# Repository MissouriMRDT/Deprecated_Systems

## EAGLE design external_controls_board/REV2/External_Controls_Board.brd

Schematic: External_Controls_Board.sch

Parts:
+5V, +12V: APPPP45_PCB_VERT; APP45_PCB_VERT
CAP_TOOL: .1µF; 0603-CAP
FET_PWRMAIN: BUK9Y4R4-40EPOWER-SO8; POWER-SO8
FET_TOOL: BUK9Y4R4-40EPOWER-SO8; POWER-SO8
GND: APPPP45_PCB_VERT; APP45_PCB_VERT
LT1910-J2, LT1910-MAIN: LT1910; SO8
LT1910CAP-MAIN: .1µF; 0603-CAP
S00, S01, S02, S03, S10, S11, S12, S13, S20, S21, S22, S23, S30, S31, S32, S33: SERVO; SERVO_JACK
U$1, U$8: SN74AHCT125; SOIC14
U$2: TIVA-C-CONNECTED
U$3, U$11: APPPP45_PCB_VERT; APP45_PCB_VERT
U$4, U$9: M07; MOLEX_43650-07
U$6: MOUNTING_HOLE#8; #8_SCREW
U$10: ACS722; SO-08

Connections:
+3V3: U$10.8 (VCC)
+5V: +5V.P$1, S00.VCC (+5V), S01.VCC (+5V), S02.VCC (+5V), S03.VCC (+5V), S10.VCC (+5V), S11.VCC (+5V), S12.VCC (+5V), S13.VCC (+5V), S20.VCC (+5V), S21.VCC (+5V), S22.VCC (+5V), S23.VCC (+5V), S30.VCC (+5V), S31.VCC (+5V), S32.VCC (+5V), S33.VCC (+5V), U$1.14 (VCC), U$2.+5V_1 (+5V), U$2.+5V_2 (+5V), U$8.14 (VCC)
+12V: CAP_TOOL.2, FET_TOOL.5 (D), FET_TOOL.6 (D), FET_TOOL.7 (D), FET_TOOL.8 (D), LT1910-J2.6 (SENSE), LT1910-J2.8 (V+), U$4.P_6 (6), U$9.P_6 (6), U$10.3 (IP-), U$10.4 (IP-)
BPWM0_3.3: U$2.PA5, U$8.12 (4A)
BPWM1_3.3: U$2.PA4, U$8.9 (3A)
BPWM2_3.3: U$2.PD5, U$8.5 (2A)
BPWM3_3.3: U$2.PD4, U$8.2 (1A)
DYNA_DATA: U$2.PC4, U$2.PC5, U$4.P_5 (5), U$9.P_5 (5)
GATE-J2: FET_TOOL.4 (G), LT1910-J2.5 (GATE)
GATE-MAIN: FET_PWRMAIN.4 (G), LT1910-MAIN.5 (GATE)
GND: CAP_TOOL.1, GND.P$1, LT1910-J2.1 (GND), LT1910-MAIN.1 (GND), LT1910CAP-MAIN.1, S00.GND, S01.GND, S02.GND, S03.GND, S10.GND, S11.GND, S12.GND, S13.GND, S20.GND, S21.GND, S22.GND, S23.GND, S30.GND, S31.GND, S32.GND, S33.GND, U$1.1 (1OE), U$1.4 (2OE), U$1.7 (GND), U$1.10 (3OE), U$1.13 (4OE), U$2.GND_1 (GND), U$2.GND_2 (GND), U$2.GND_3 (GND), U$2.GND_4 (GND), U$4.P_7 (7), U$8.1 (1OE), U$8.4 (2OE), U$8.7 (GND), U$8.10 (3OE), U$8.13 (4OE), U$9.P_7 (7), U$10.5 (GND), U$10.6 (FILTER), U$11.P$1
IMEAS_12V_MAIN: U$2.PB4, U$10.7 (VIOUT)
unnamed: +12V.P$1, FET_PWRMAIN.5 (D), FET_PWRMAIN.6 (D), FET_PWRMAIN.7 (D), FET_PWRMAIN.8 (D), LT1910-MAIN.6 (SENSE), LT1910-MAIN.8 (V+), LT1910CAP-MAIN.2
P00: S00.SIGNAL (SIG), U$2.PK0
P01: S01.SIGNAL (SIG), U$2.PK1
P02: S02.SIGNAL (SIG), U$2.PK2
P03: S03.SIGNAL (SIG), U$2.PK3
P10: S10.SIGNAL (SIG), U$2.PP0
P11: S11.SIGNAL (SIG), U$2.PP1
P12: S12.SIGNAL (SIG), U$2.PN4
P13: S13.SIGNAL (SIG), U$2.PN5
P20: S20.SIGNAL (SIG), U$2.PL0
P21: S21.SIGNAL (SIG), U$2.PL1
P22: S22.SIGNAL (SIG), U$2.PL2
P23: S23.SIGNAL (SIG), U$2.PL3
P30: S30.SIGNAL (SIG), U$2.PF1
P31: S31.SIGNAL (SIG), U$2.PF2
P32: S32.SIGNAL (SIG), U$2.PF3
P33: S33.SIGNAL (SIG), U$2.PH2
PWM0_1: U$8.11 (4Y), U$9.P_4 (4)
PWM0_3.3: U$1.12 (4A), U$2.PE3
PWM0_5: U$1.11 (4Y), U$4.P_4 (4)
PWM1_1: U$8.8 (3Y), U$9.P_3 (3)
PWM1_3.3: U$1.9 (3A), U$2.PE2
PWM1_5: U$1.8 (3Y), U$4.P_3 (3)
PWM2_1: U$8.6 (2Y), U$9.P_2 (2)
PWM2_3.3: U$1.5 (2A), U$2.PE1
PWM2_5: U$1.6 (2Y), U$4.P_2 (2)
PWM3_1: U$8.3 (1Y), U$9.P_1 (1)
PWM3_3.3: U$1.2 (1A), U$2.PE0
PWM3_5: U$1.3 (1Y), U$4.P_1 (1)
SERVO_SIG_8: U$2.PM0
SERVO_SIG_10: U$2.PM2
SERVO_SIG_11: U$2.PM3
SERVO_SIG_12: U$2.PM4
SERVO_SIG_13: U$2.PM5
SERVO_SIG_15: U$2.PM7
SIG_MAIN: LT1910-MAIN.4 (IN), U$2.PM6
SOURCE-MAIN: FET_PWRMAIN.1 (S), FET_PWRMAIN.2 (S), FET_PWRMAIN.3 (S), U$10.1 (IP+), U$10.2 (IP+)
TOOL: FET_TOOL.1 (S), FET_TOOL.2 (S), FET_TOOL.3 (S), U$3.P$1
TOOL_CHANGE_ENABLE: LT1910-J2.4 (IN)

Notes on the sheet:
MAIN POWER
J2 POWER

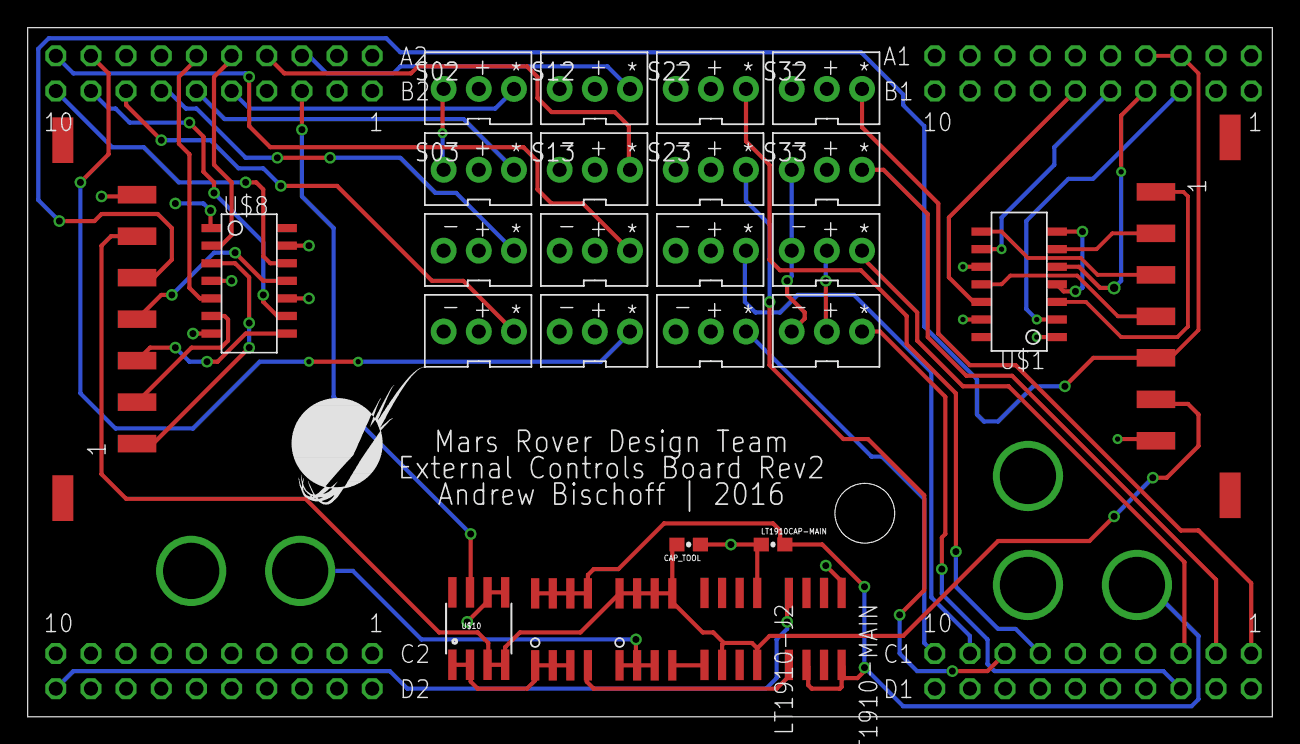
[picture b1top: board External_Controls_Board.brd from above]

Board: 2 copper layers, 89.9 x 49.8 mm, 36 parts (0 on the bottom side), 43 nets.

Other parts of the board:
U$5: MOUNTING_HOLE#8; #8_SCREW
U$7: MRDT_LOGO

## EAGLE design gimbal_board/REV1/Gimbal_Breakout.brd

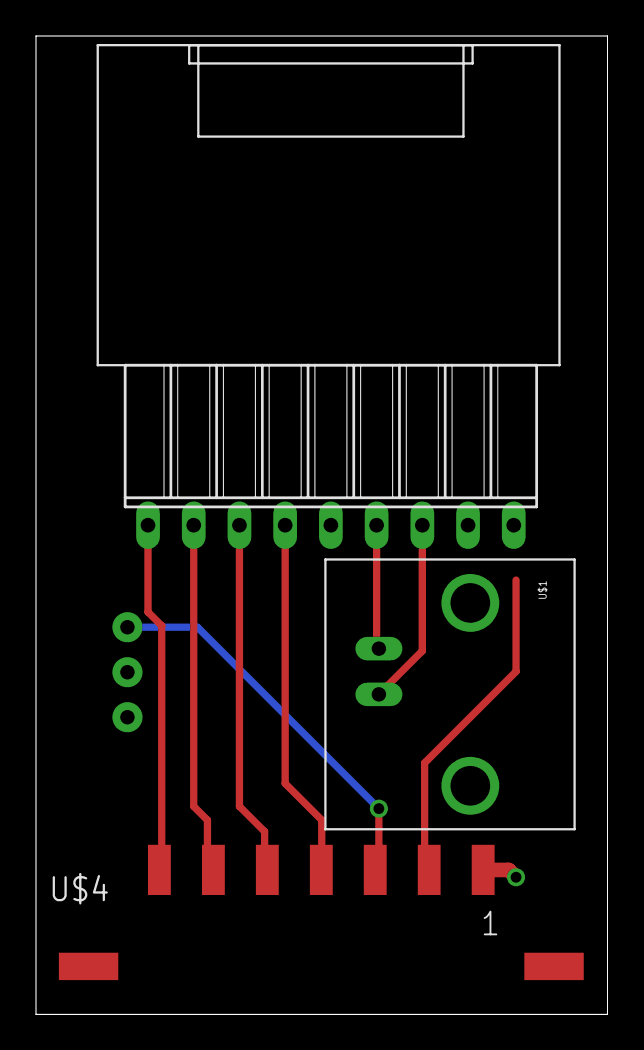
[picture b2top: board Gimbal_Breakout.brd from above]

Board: 2 copper layers, 31.8 x 54.4 mm, 4 parts (0 on the bottom side), 9 nets.

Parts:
DYNA2: DYNAMIXEL-1X03HORIZ; MLX-SPOX5268-3PIN
U$1: BNCPTH; BNC
U$3: M07; MOLEX_43650-07
U$4: CAMERA_BREAKOUT; CAM_CONNECTOR

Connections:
+12V: DYNA2.VCC, U$3.P_2, U$4.8
CAM_PWM0: U$3.P_4, U$4.4
CAM_PWM1: U$3.P_5, U$4.3
CAM_PWM2: U$3.P_6, U$4.2
CAM_PWM3: U$3.P_7, U$4.1
CAM_VIDEO: U$1.S, U$4.7
CAM_VIDEO_GND: U$1.GND, U$4.6
DYNA_DATA: DYNA2.DATA, U$3.P_3
GND: DYNA2.GND, U$3.P_1, U$4.9

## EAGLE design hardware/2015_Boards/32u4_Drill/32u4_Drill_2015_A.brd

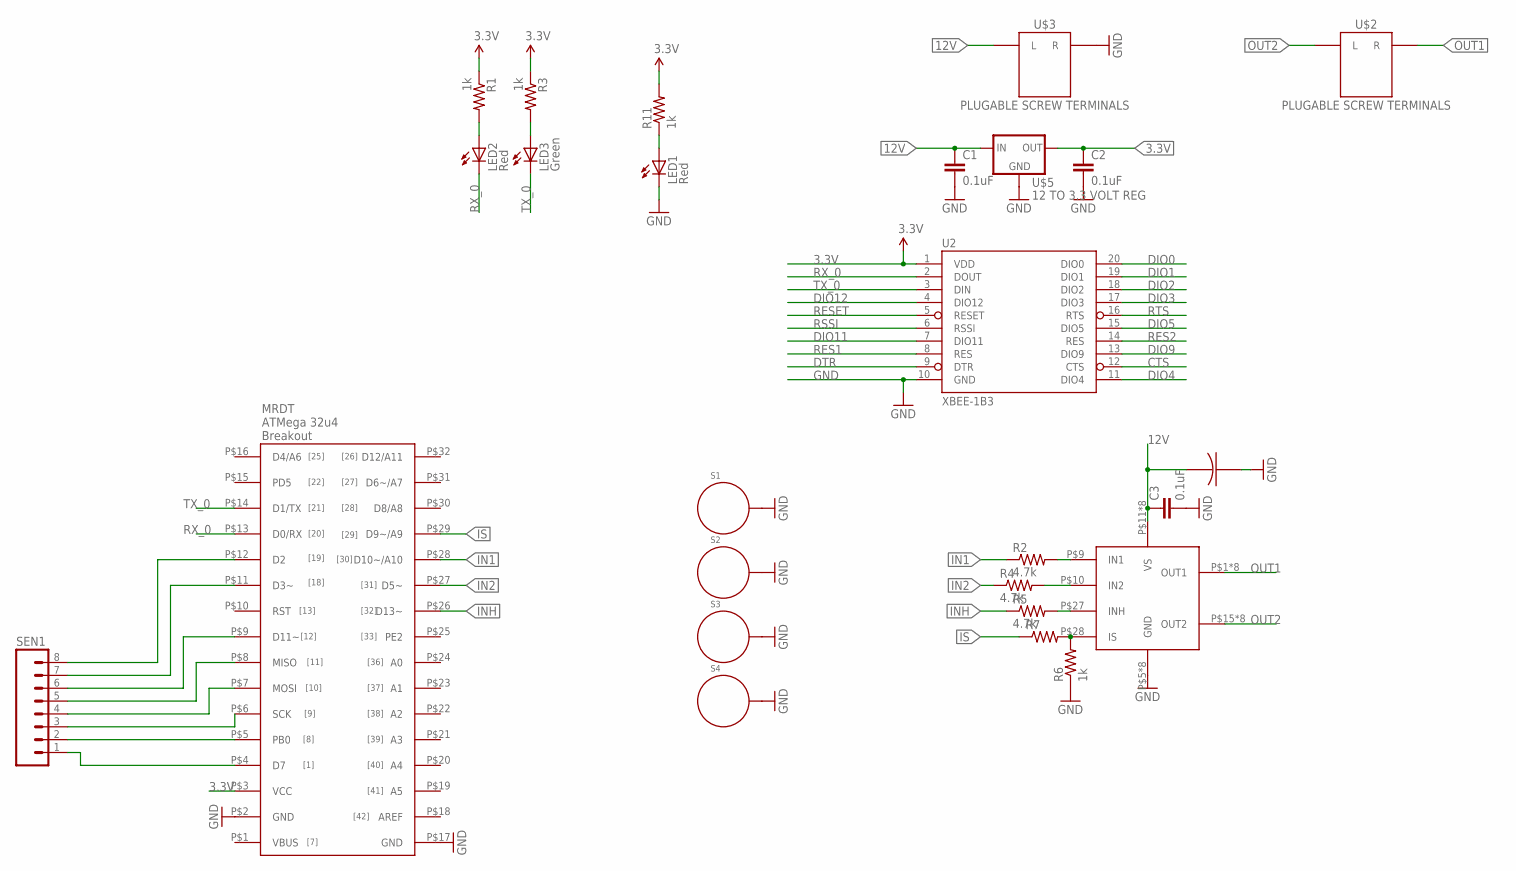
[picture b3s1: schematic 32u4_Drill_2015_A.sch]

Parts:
C1, C2, C3: 0.1uF; 1206
LED1, LED2: Red; LED-0603
LED3: Green; LED-0603
R1, R3, R6, R11: 1k; 1206
R2, R4, R5: 4.7k; 1206
R7: RESISTOR1206; 1206
S1, S2, S3, S4: STANDOFF_ELECTRICAL; STANDOFF-ELECTRICAL
SEN1: M081X08; 1X08
U2: XBEE-1B3; XBEE-SMD
U$1: 32U4_BREAKOU_SMD; 32U3_MCU_DIP_SMD
U$2, U$3: PLUGABLE SCREW TERMINALS; 691321100002
U$4: BTM7752G
U$5: 12 TO 3.3 VOLT REG; SOT223
U$6: 100UF-ELECTRO-CAP; ELECTRO-CAP

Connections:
12V: C1.1, C3.1, U$3.L, U$4.P$11 (VS), U$4.P$12 (VS), U$4.P$13 (VS), U$4.P$14 (VS), U$4.P$29 (VS), U$4.P$30 (VS), U$4.P$31 (VS), U$4.P$32 (VS), U$5.1 (IN), U$6.POS
CTS: U2.12 (CTS)
DIO0: U2.20 (DIO0)
DIO1: U2.19 (DIO1)
DIO2: U2.18 (DIO2)
DIO3: U2.17 (DIO3)
DIO4: U2.11 (DIO4)
DIO5: U2.15 (DIO5)
DIO9: U2.13 (DIO9)
DIO11: U2.7 (DIO11)
DIO12: U2.4 (DIO12)
DTR: U2.9 (DTR)
GND: C1.2, C2.2, C3.2, LED1.C, R6.1, S1.P1, S2.P1, S3.P1, S4.P1, U2.10 (GND), U$1.P$2 (GND), U$1.P$17 (GND), U$3.R, U$4.P$5 (GND), U$4.P$6 (GND), U$4.P$7 (GND), U$4.P$8 (GND), U$4.P$23 (GND), U$4.P$24 (GND), U$4.P$25 (GND), U$4.P$26 (GND), U$5.2 (GND), U$5.4 (GND), U$6.NEG
IN1: R2.1, U$1.P$28 (D10~/A10)
IN2: R4.1, U$1.P$27 (D5~)
INH: R5.1, U$1.P$26 (D13~)
IS: R7.1, U$1.P$29 (D9~/A9)
unnamed: LED2.A, R1.2
unnamed: R2.2, U$4.P$9 (IN1)
unnamed: R4.2, U$4.P$10 (IN2)
unnamed: LED3.A, R3.2
unnamed: R5.2, U$4.P$27 (INH)
unnamed: R6.2, R7.2, U$4.P$28 (IS)
unnamed: SEN1.1, U$1.P$4 (D7)
unnamed: SEN1.2, U$1.P$5 (PB0)
unnamed: SEN1.3, U$1.P$6 (SCK)
unnamed: SEN1.4, U$1.P$7 (MOSI)
unnamed: SEN1.5, U$1.P$8 (MISO)
unnamed: SEN1.6, U$1.P$9 (D11~)
unnamed: SEN1.7, U$1.P$11 (D3~)
unnamed: LED1.A, R11.1
OUT1: U$2.R, U$4.P$1 (OUT1), U$4.P$2 (OUT1), U$4.P$3 (OUT1), U$4.P$4 (OUT1), U$4.P$33 (OUT1), U$4.P$34 (OUT1), U$4.P$35 (OUT1), U$4.P$36 (OUT1)
OUT2: U$2.L, U$4.P$15 (OUT2), U$4.P$16 (OUT2), U$4.P$17 (OUT2), U$4.P$18 (OUT2), U$4.P$19 (OUT2), U$4.P$20 (OUT2), U$4.P$21 (OUT2), U$4.P$22 (OUT2)
RES1: U2.8 (RES)
RES2: U2.14 (RES)
RESET: U2.5 (RESET)
RSSI: U2.6 (RSSI)
RTS: U2.16 (RTS)
RX_0: LED2.C, U2.2 (DOUT), U$1.P$13 (D0/RX)
TX_0: LED3.C, U2.3 (DIN), U$1.P$14 (D1/TX)

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
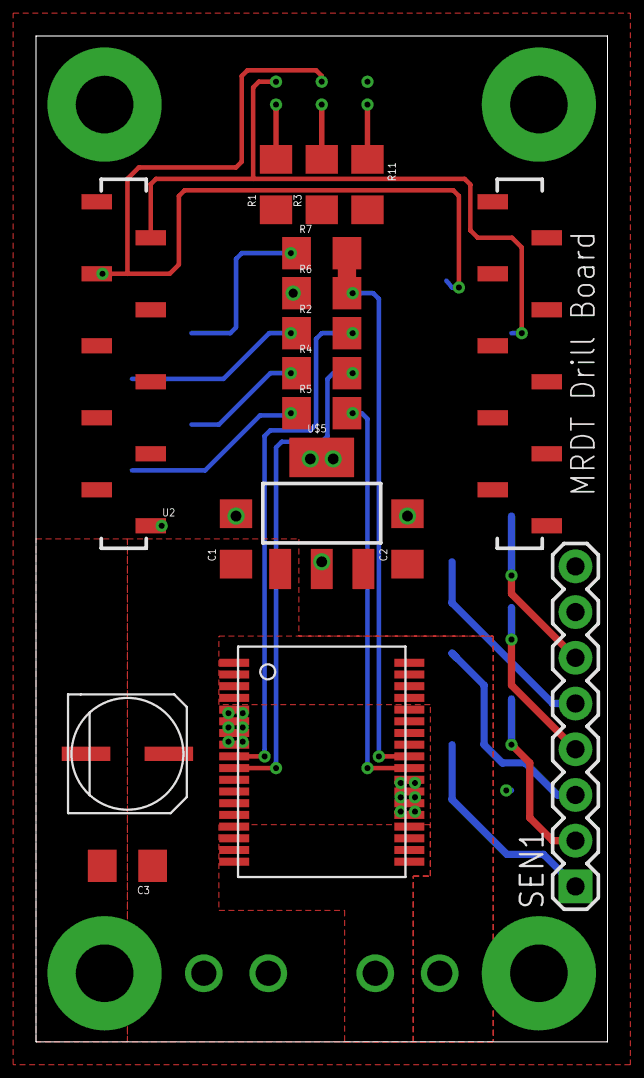
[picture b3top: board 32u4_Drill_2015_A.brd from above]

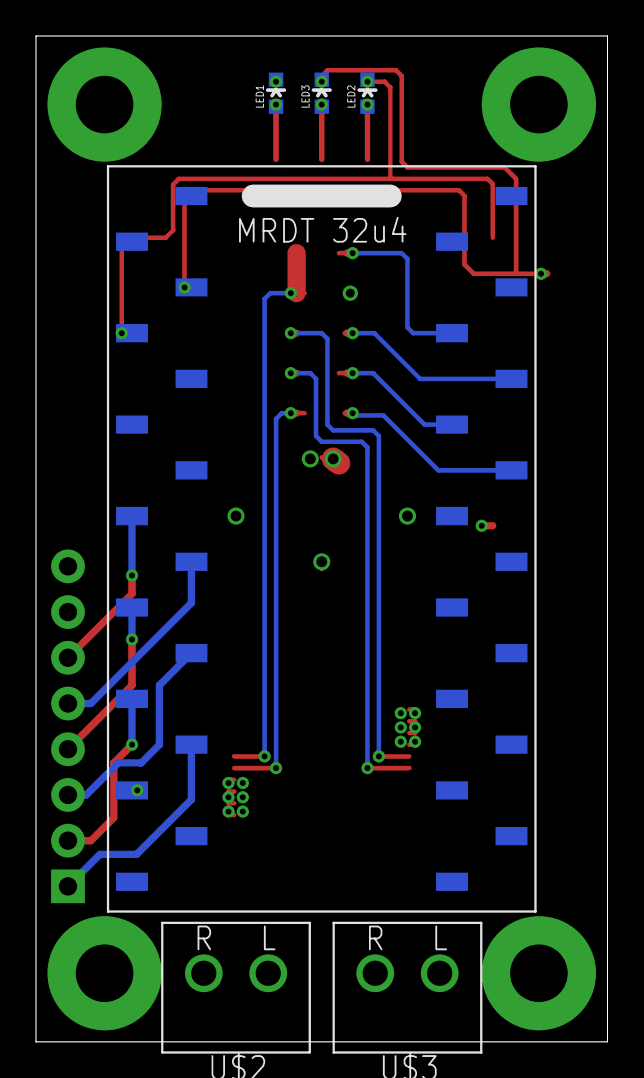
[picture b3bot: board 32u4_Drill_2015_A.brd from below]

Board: 2 copper layers, 31.8 x 55.9 mm, 26 parts (6 on the bottom side), 24 nets.

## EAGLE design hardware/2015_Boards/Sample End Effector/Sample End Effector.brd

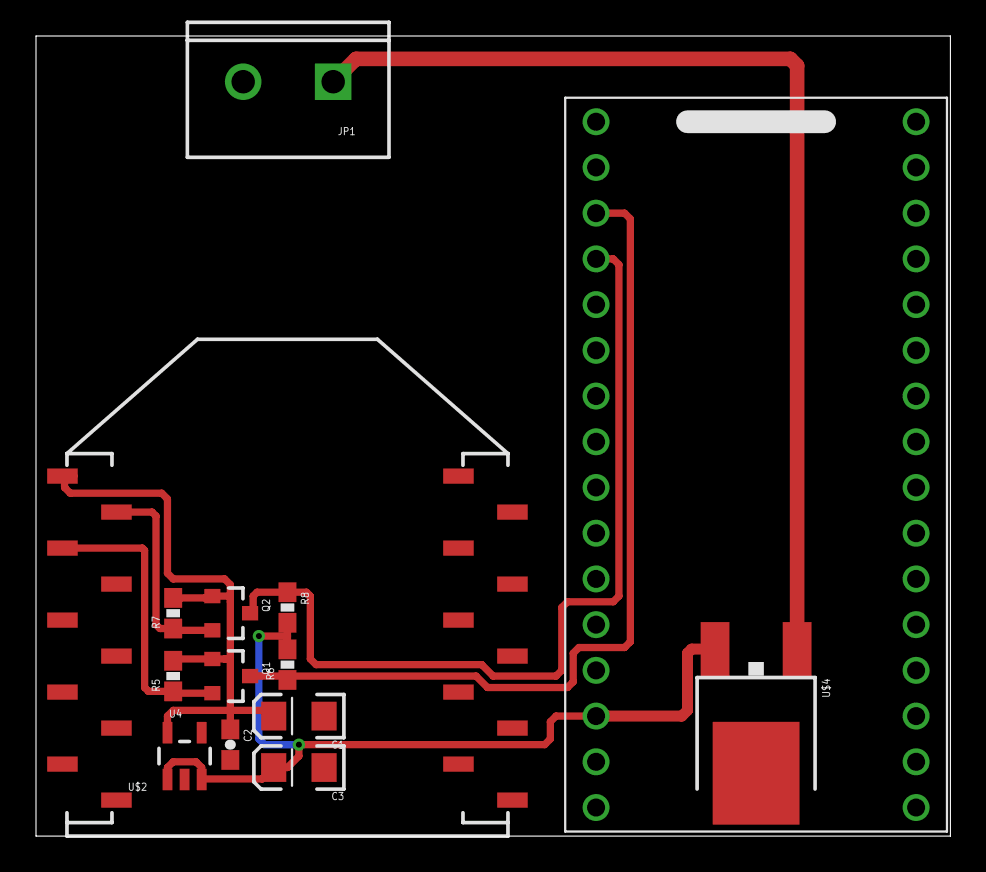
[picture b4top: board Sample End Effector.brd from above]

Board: 2 copper layers, 50.8 x 44.5 mm, 14 parts (0 on the bottom side), 8 nets.

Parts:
C1, C3: 10uF; EIA3216
C2: 0.1uF; 0603-CAP
JP1: M025MM; SCREWTERMINAL-5MM-2
Q1, Q2: MOSFET-NCHANNELSMD; SOT23-3
R5, R6, R7, R8: 1k; 0603-RES
U4: V_REG_LDOSMD; SOT23-5
U$1: 32U4; DIP
U$2: XBEE-1B3; XBEE-SMD
U$4: LM2931_FIXED; DPAK

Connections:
3.3V: C1.A, C2.1, Q1.1, Q2.1, R5.2, R7.2, U4.5, U$2.1
5V: C3.A, R6.2, R8.2, U4.1, U4.3, U$1.14, U$4.3
12V: JP1.1, U$4.1
DIN: Q1.2, R5.1, U$2.3
DOUT: Q2.2, R7.1, U$2.2
GND: C1.C, C2.2, C3.C, JP1.2, U4.2, U$1.15, U$1.17, U$2.10, U$4.4
RX: Q2.3, R8.1, U$1.4
TX: Q1.3, R6.1, U$1.3

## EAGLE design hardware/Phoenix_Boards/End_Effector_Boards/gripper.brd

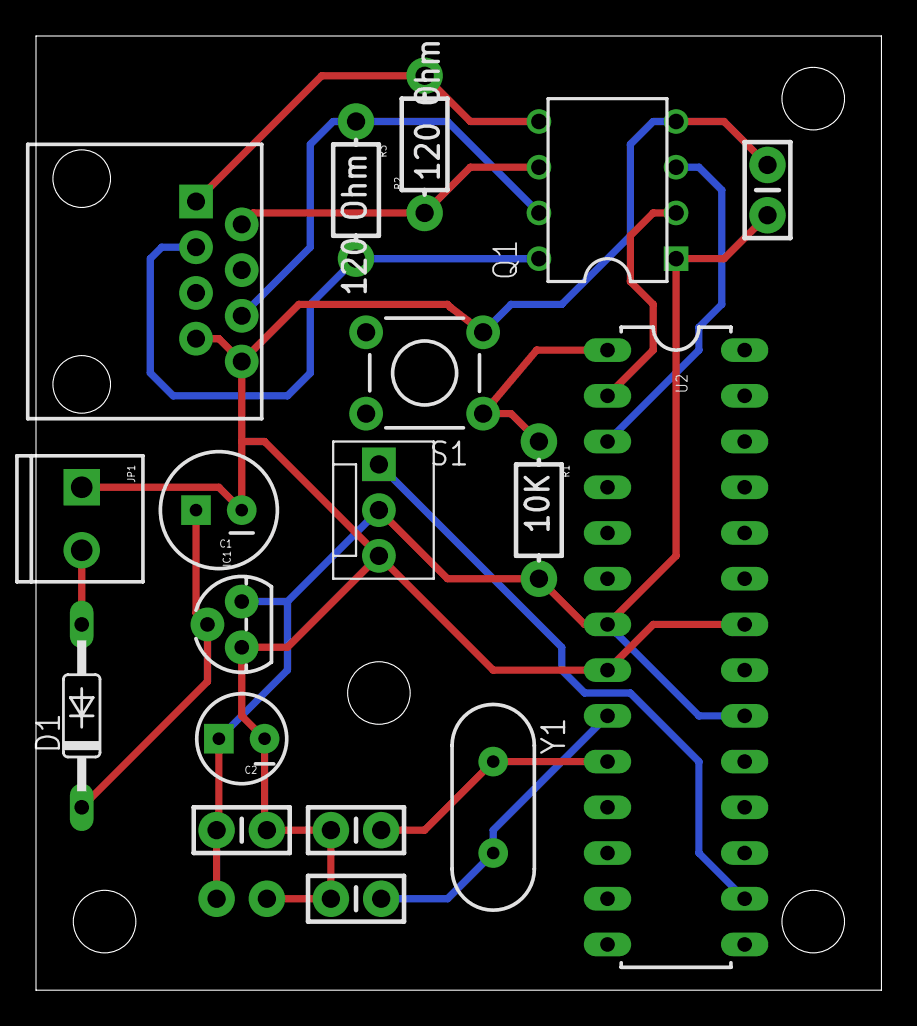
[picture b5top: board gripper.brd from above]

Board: 2 copper layers, 47.0 x 53.0 mm, 19 parts (1 on the bottom side), 14 nets.

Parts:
C1: 100uF; CPOL-RADIAL-100UF-25V
C2: 10uF; CPOL-RADIAL-10UF-25V
C3, C7: .1uF; CAP-PTH-SMALL-KIT
C4, C5: 22pF; CAP-PTH-SMALL-KIT
C6: .01uF; CAP-PTH-SMALL-KIT
D1: 1N4446; DO35-10
IC1: TO-92
JP1: M023.5MM; SCREWTERMINAL-3.5MM-2
JP2: MOLEX-1X3
Q1: Q_LTC490; DIP8
R1: 10K; AXIAL-0.3-KIT
R2, R3: 120 Ohm; AXIAL-0.3-KIT
S1: SWITCH-MOMENTARY-2PTH; TACTILE-PTH
U2: ATMEGA328P_PDIP; DIL28-3
U$1: RJ45-8PTH; RJ45-8
Y1: 16MHz; HC49US

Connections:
GND: C1.2, C2.2, C3.1, C4.2, C5.2, C6.1, C7.1, IC1.1, JP1.1, JP2.3, Q1.4, S1.3, U2.8, U2.22, U$1.7, U$1.8
unnamed: D1.A, JP1.2
unnamed: C1.1, D1.C, IC1.2
unnamed: C2.1, C3.2, C6.2, C7.2, IC1.3, JP2.2, Q1.1, R1.P$2, U2.7, U2.20
unnamed: R1.P$1, S1.1, U2.1
unnamed: Q1.5, R2.P$2, U$1.1
unnamed: C4.1, U2.9, Y1.2
unnamed: C5.1, U2.10, Y1.1
unnamed: JP2.1, U2.16
unnamed: Q1.2, U2.2
unnamed: Q1.3, U2.3
unnamed: Q1.8, R3.P$2, U$1.3
unnamed: Q1.6, R2.P$1, U$1.2
unnamed: Q1.7, R3.P$1, U$1.6

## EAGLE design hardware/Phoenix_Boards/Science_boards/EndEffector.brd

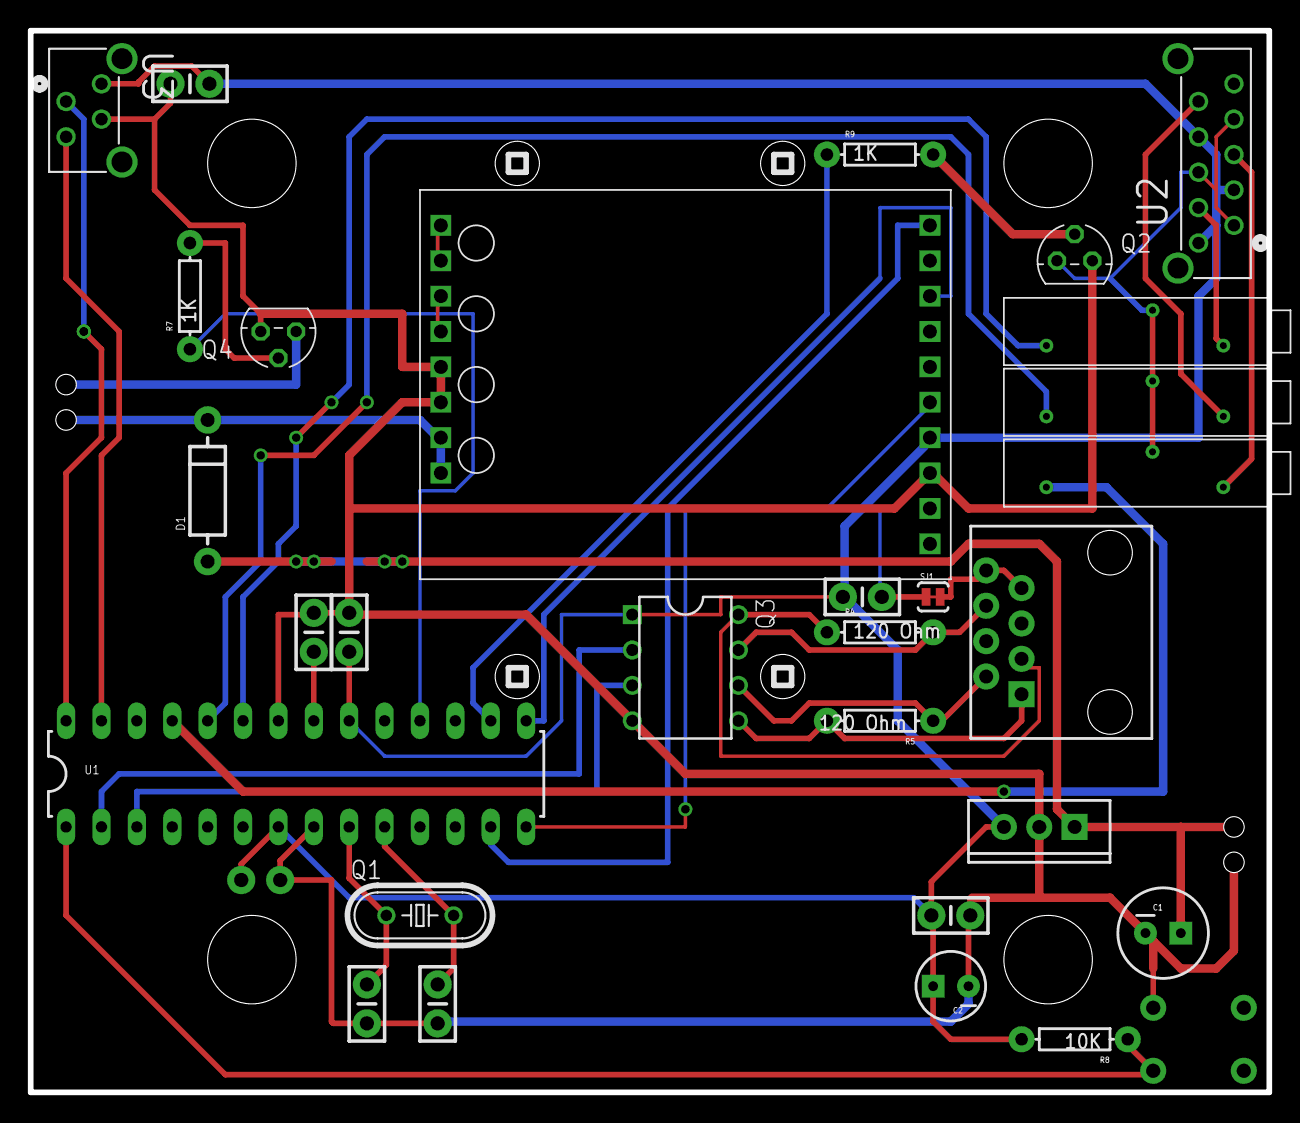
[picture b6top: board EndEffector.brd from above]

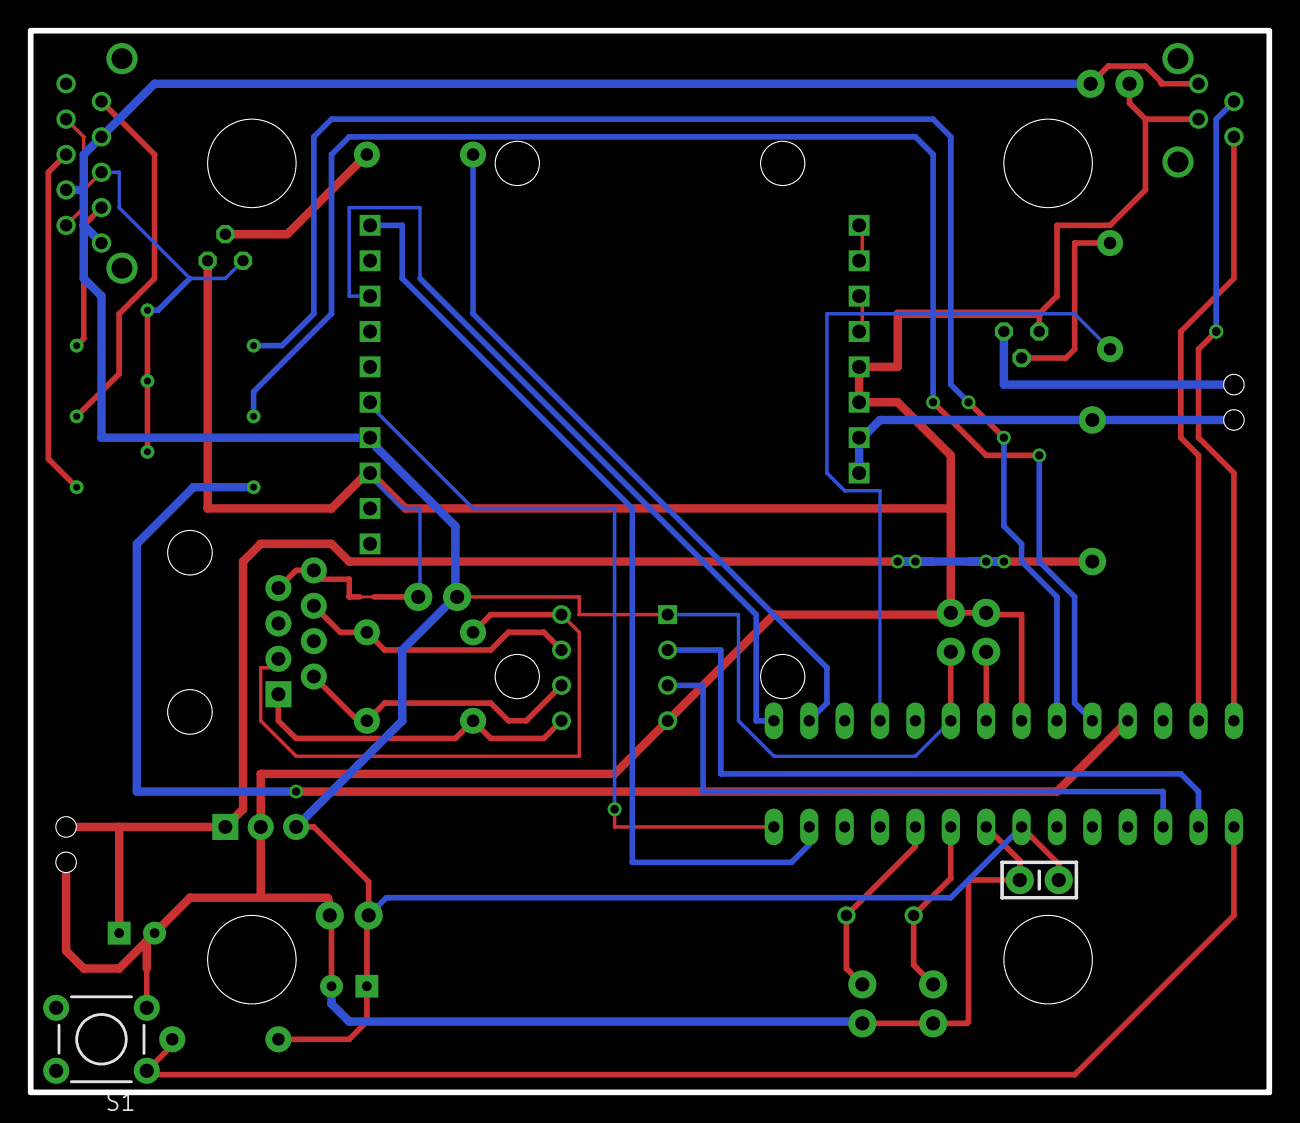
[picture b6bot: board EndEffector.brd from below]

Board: 2 copper layers, 88.9 x 76.2 mm, 33 parts (2 on the bottom side), 34 nets.

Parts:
C1: 100uF; CPOL-RADIAL-100UF-25V
C2: 10uF; CPOL-RADIAL-10UF-25V
C3, C9, C10: .1uF; CAP-PTH-SMALL-KIT
C4, C5: 22pF; CAP-PTH-SMALL-KIT
C6, C7, C8: .01uF; CAP-PTH-SMALL-KIT
D1: DIODE-1N4001
IC1: TO220-IGO
JP1, JP2: M02; 1X02_PP_HOLES_ONLY
Q1: 16MHZ; HC49/S
Q2, Q4: BC517; TO92
Q3: Q_LTC490; DIP8
R4, R5: 120 Ohm; AXIAL-0.3
R7, R9: 1K; AXIAL-0.3
R8: 10K; AXIAL-0.3
S1: SWITCH-MOMENTARY-2PTH; TACTILE-PTH
SJ1: SOLDERJUMPERTRACE; SJ_2S-TRACE
U1: ATMEGA328P_PDIP; DIL28-3
U2: 90325-0010; MOLEX_90325-0010
U3: 90325-0004; MOLEX_90325-0004
U$1: RJ45-8PTH; RJ45-8
U$2, U$4, U$5: BOURNS30006_TRIMPOT
U$6: VNH5019_POLOLU_CARRIER; VNH5019_CARRIER

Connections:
5V+: C2.1, C3.1, C6.1, C7.1, C9.1, C10.1, IC1.OUT, Q3.1, R8.P$2, U1.7, U1.20, U2.1, U2.4, U2.7, U3.1, U$6.VDD
12V+: D1.C, JP1.1, U$6.VIN_MOT_1, U$6.VIN_MOT_2
ADC0: U1.23, U$4.1
ADC1: U1.24, U$5.1
ADC2: U1.25, U$2.1
AMMONIA: U2.6, U$2.3
GAS_CTRL: R9.P$1, U1.16
GAS_GND: Q2.3, U2.2, U2.5, U2.8, U$2.2, U$4.2, U$5.2
GND: C1.2, C2.2, C3.2, C4.1, C5.2, C6.2, C7.2, C8.1, C9.2, C10.2, IC1.GND, JP2.1, Q2.1, Q3.4, Q4.1, S1.3, SJ1.1, U1.8, U1.22, U3.3, U$6.GND, U$6.GND_1, U$6.GND_2
HEAT_CTRL: R7.P$1, U1.18
HYDROGEN: U2.9, U$5.3
IR_SCL: U1.28, U3.2
IR_SDA: U1.27, U3.4
METHANE: U2.3, U$4.3
MOT_INA: U1.13, U$6.INA
MOT_INB: U1.14, U$6.INB
MOT_PWM: U1.15, U$6.PWM
unnamed: JP1.2, Q4.3
unnamed: Q2.2, R9.P$2
unnamed: U$6.OUTA_1, U$6.OUTA_2
unnamed: C5.1, Q1.2, U1.10
unnamed: Q3.5, R5.P$2, U$1.1
unnamed: C4.2, Q1.1, U1.9
unnamed: SJ1.2, U$1.7, U$1.8
unnamed: Q3.6, R5.P$1, U$1.2
unnamed: Q3.7, R4.P$2, U$1.6
unnamed: Q3.8, R4.P$1, U$1.3
unnamed: R8.P$1, S1.1, U1.1
unnamed: Q4.2, R7.P$2
unnamed: U$6.OUTB_1, U$6.OUTB_2
unnamed: C8.2, U1.21
RXD: Q3.2, U1.2
TXD: Q3.3, U1.3
VCC: C1.1, D1.A, IC1.IN, JP2.2

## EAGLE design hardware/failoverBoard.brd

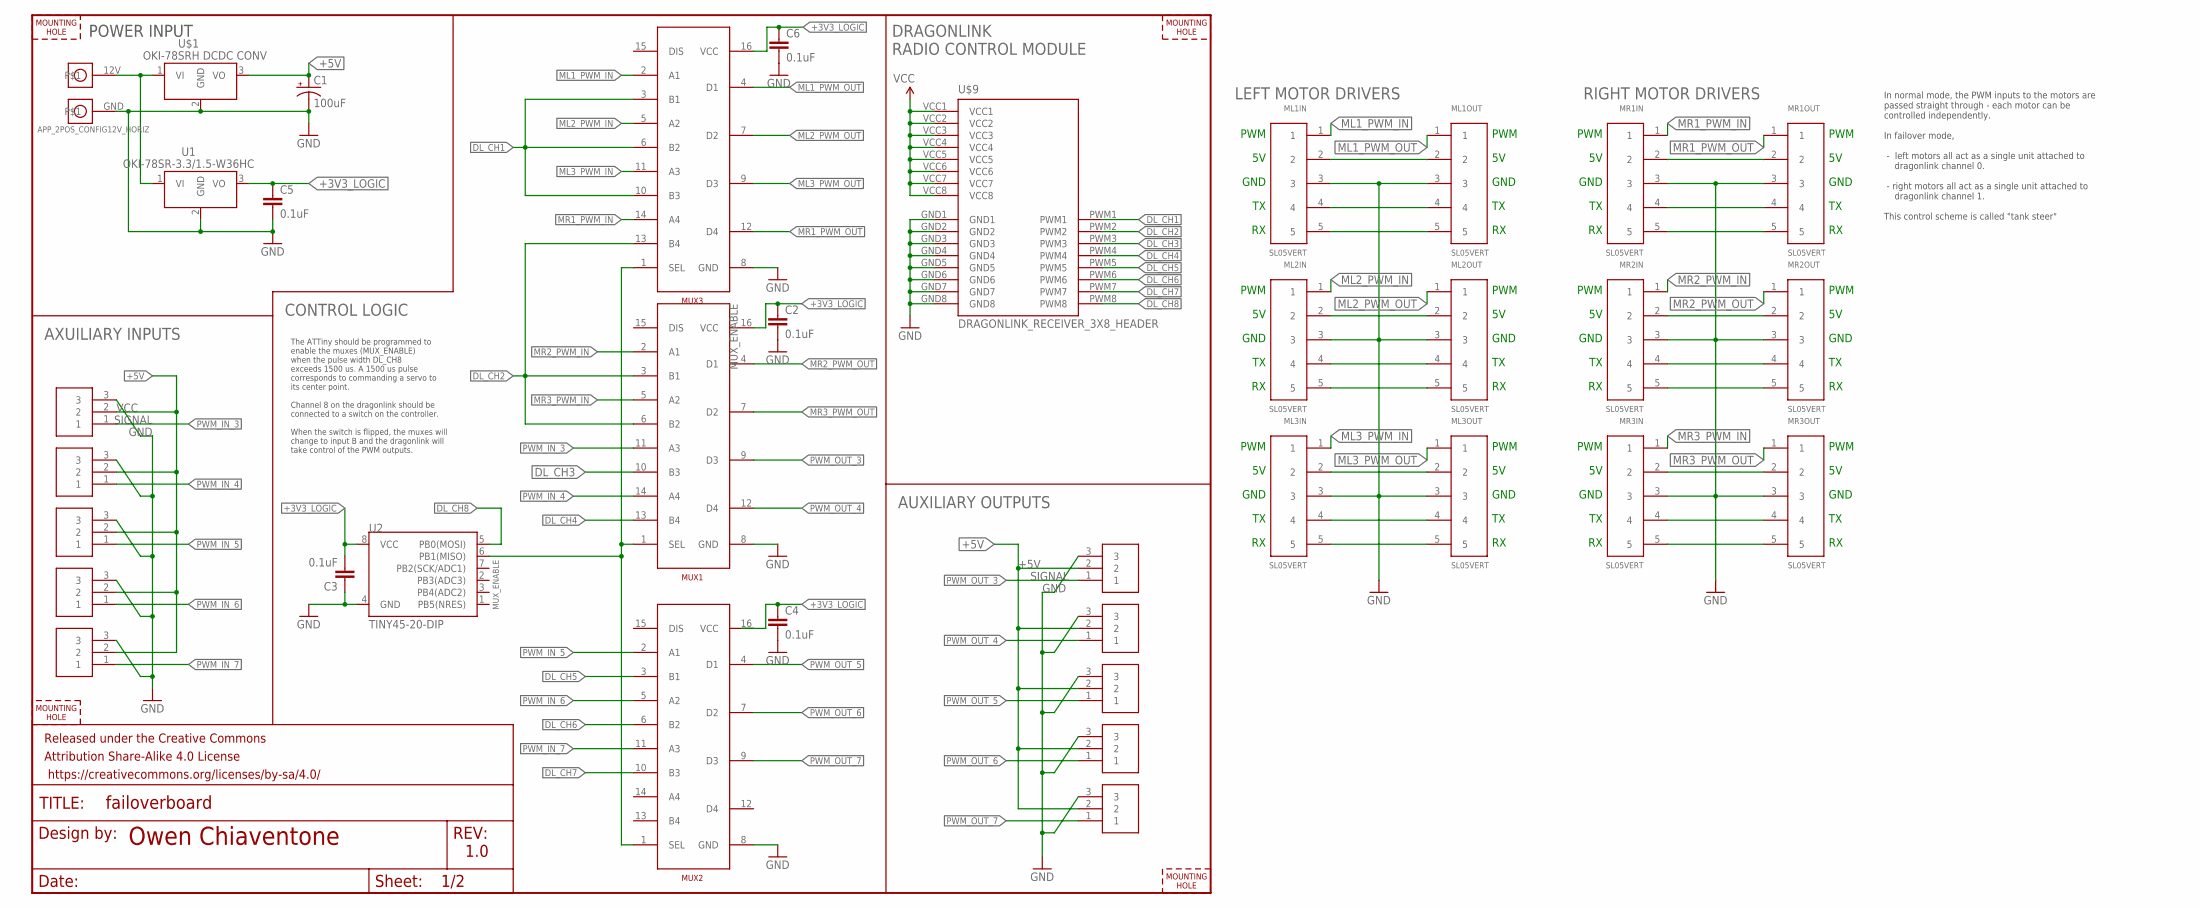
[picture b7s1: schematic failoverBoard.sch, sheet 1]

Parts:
C1: 100uF; C_3.5MM
C2, C3, C4, C6: 0.1uF; BOOST_CMP_0603-CAP
C5: 0.1uF; 0603-CAP
FRAME1: FRAME-LETTER; CREATIVE_COMMONS
IN3, IN4, IN5, IN6, IN7: SIERRAALTO.CONN.SUPPLEMENT_CONN_3MOLEX_0705550037; SIERRAALTO.CONN.SUPPLEMENT_MOLEX_0705550037_3
J1: APP_2POS_CONFIG12V_HORIZ; APP45_12V_HORIZ_CONFIG
ML1IN, ML1OUT, ML2IN, ML2OUT, ML3IN, ML3OUT: SL05VERT; MOLEX-70543-0004
MR1IN, MR1OUT, MR2IN, MR2OUT, MR3IN, MR3OUT: SL05VERT; MOLEX-70543-0004
MUX1, MUX2, MUX3: CD40257; SOIC16
OUT3, OUT4, OUT5, OUT6, OUT7: SIERRAALTO.CONN.SUPPLEMENT_CONN_3MOLEX_0705550037; SIERRAALTO.CONN.SUPPLEMENT_MOLEX_0705550037_3
U1: OKI-78SR-3.3/1.5-W36HC; OKI-78SR_HORIZ
U2: TINY45-20-DIP; DIP08
U$1: Q_OKI-78SR; OKI-78SR_HORIZ
U$3, U$4, U$5, U$6: MOUNTING_HOLE#6; #6_SCREW
U$9: DRAGONLINK_RECEIVER_3X8_HEADER; 3X8_HEADER_2.54MM

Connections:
+3V3_LOGIC: C2.1, C3.2, C4.1, C5.1, C6.1, MUX1.16 (VCC), MUX2.16 (VCC), MUX3.16 (VCC), U1.3 (VO), U2.8 (VCC)
+5V: C1.+, IN3.2, IN4.2, IN5.2, IN6.2, IN7.2, OUT3.2, OUT4.2, OUT5.2, OUT6.2, OUT7.2, U$1.3 (VO)
DL_CH1: MUX3.3 (B1), MUX3.6 (B2), MUX3.10 (B3), U$9.PWM1
DL_CH2: MUX1.3 (B1), MUX1.6 (B2), MUX3.13 (B4), U$9.PWM2
DL_CH3: MUX1.10 (B3), U$9.PWM3
DL_CH4: MUX1.13 (B4), U$9.PWM4
DL_CH5: MUX2.3 (B1), U$9.PWM5
DL_CH6: MUX2.6 (B2), U$9.PWM6
DL_CH7: MUX2.10 (B3), U$9.PWM7
DL_CH8: U2.5 (PB0(MOSI)), U$9.PWM8
GND: C1.-, C2.2, C3.1, C4.2, C5.2, C6.2, IN3.3, IN4.3, IN5.3, IN6.3, IN7.3, J1.GND, ML1IN.3, ML1OUT.3, ML2IN.3, ML2OUT.3, ML3IN.3, ML3OUT.3, MR1IN.3, MR1OUT.3, MR2IN.3, MR2OUT.3, MR3IN.3, MR3OUT.3, MUX1.8 (GND), MUX2.8 (GND), MUX3.8 (GND), OUT3.3, OUT4.3, OUT5.3, OUT6.3, OUT7.3, U1.2 (GND), U2.4 (GND), U$1.2 (GND), U$9.GND1, U$9.GND2, U$9.GND3, U$9.GND4, U$9.GND5, U$9.GND6, U$9.GND7, U$9.GND8
ML1_PWM_IN: ML1IN.1, MUX3.2 (A1)
ML1_PWM_OUT: ML1OUT.1, MUX3.4 (D1)
ML2_PWM_IN: ML2IN.1, MUX3.5 (A2)
ML2_PWM_OUT: ML2OUT.1, MUX3.7 (D2)
ML3_PWM_IN: ML3IN.1, MUX3.11 (A3)
ML3_PWM_OUT: ML3OUT.1, MUX3.9 (D3)
MR1_PWM_IN: MR1IN.1, MUX3.14 (A4)
MR1_PWM_OUT: MR1OUT.1, MUX3.12 (D4)
MR2_PWM_IN: MR2IN.1, MUX1.2 (A1)
MR2_PWM_OUT: MR2OUT.1, MUX1.4 (D1)
MR3_PWM_IN: MR3IN.1, MUX1.5 (A2)
MR3_PWM_OUT: MR3OUT.1, MUX1.7 (D2)
MUX_ENABLE: MUX1.1 (SEL), MUX2.1 (SEL), MUX3.1 (SEL), U2.6 (PB1(MISO))
unnamed: J1.12V, U1.1 (VI), U$1.1 (VI)
unnamed: ML1IN.4, ML1OUT.4
unnamed: ML2IN.4, ML2OUT.4
unnamed: ML2IN.5, ML2OUT.5
unnamed: ML1IN.5, ML1OUT.5
unnamed: ML3IN.4, ML3OUT.4
unnamed: ML3IN.5, ML3OUT.5
unnamed: ML3IN.2, ML3OUT.2
unnamed: ML2IN.2, ML2OUT.2
unnamed: ML1IN.2, ML1OUT.2
unnamed: MR1IN.2, MR1OUT.2
unnamed: MR1IN.4, MR1OUT.4
unnamed: MR1IN.5, MR1OUT.5
unnamed: MR2IN.4, MR2OUT.4
unnamed: MR2IN.5, MR2OUT.5
unnamed: MR3IN.4, MR3OUT.4
unnamed: MR3IN.5, MR3OUT.5
unnamed: MR3IN.2, MR3OUT.2
unnamed: MR2IN.2, MR2OUT.2
PWM_IN_3: IN3.1, MUX1.11 (A3)
PWM_IN_4: IN4.1, MUX1.14 (A4)
PWM_IN_5: IN5.1, MUX2.2 (A1)
PWM_IN_6: IN6.1, MUX2.5 (A2)
PWM_IN_7: IN7.1, MUX2.11 (A3)
PWM_OUT_3: MUX1.9 (D3), OUT3.1
PWM_OUT_4: MUX1.12 (D4), OUT4.1
PWM_OUT_5: MUX2.4 (D1), OUT5.1
PWM_OUT_6: MUX2.7 (D2), OUT6.1
PWM_OUT_7: MUX2.9 (D3), OUT7.1
VCC: U$9.VCC1, U$9.VCC2, U$9.VCC3, U$9.VCC4, U$9.VCC5, U$9.VCC6, U$9.VCC7, U$9.VCC8

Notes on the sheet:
AXUILIARY INPUTS
AUXILIARY OUTPUTS
SIGNAL
POWER INPUT
VCC
CONTROL LOGIC
DRAGONLINK RADIO CONTROL MODULE
The ATTiny should be programmed to enable the muxes (MUX_ENABLE) when the pulse width DL_CH8 exceeds 1500 us. A 1500 us pulse corresponds to commanding a servo to its center point. Channel 8 on the dragonlink should be connected to a switch on the controller. When the switch is flipped, the muxes w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
Owen Chiaventone
1.0
PWM
GND
LEFT MOTOR DRIVERS
RIGHT MOTOR DRIVERS
In normal mode, the PWM inputs to the motors are passed straight through - each motor can be controlled independently. In failover mode, - left motors all act as a single unit attached to dragonlink channel 0. - right motors all act as a single unit attached to dragonlink channel 1. This control sc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

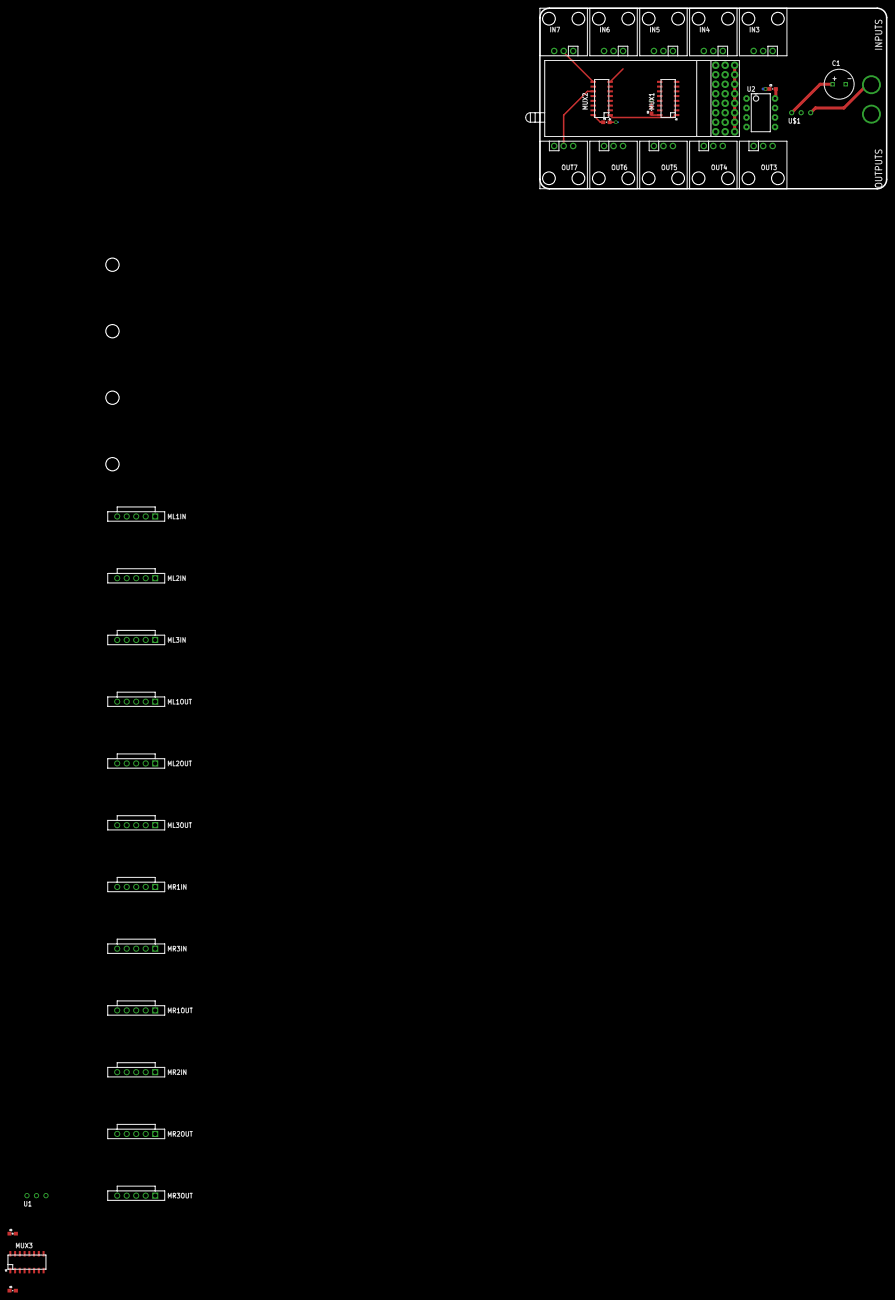
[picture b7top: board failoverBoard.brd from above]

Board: 2 copper layers, 42 parts (1 on the bottom side), 54 nets.

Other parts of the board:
U$2: MRDT_LOGO

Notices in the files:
parts and their libraries:
SparkFun-Capacitors: Licensing: Creative Commons ShareAlike 4.0 International - https://creativecommons.org/licenses/by-sa/4.0
SparkFun-Aesthetics: Licensing: CC v3.0 Share-Alike You are welcome to use this library for commercial purposes.
SparkFun-Aesthetics: Released under the Creative Commons
